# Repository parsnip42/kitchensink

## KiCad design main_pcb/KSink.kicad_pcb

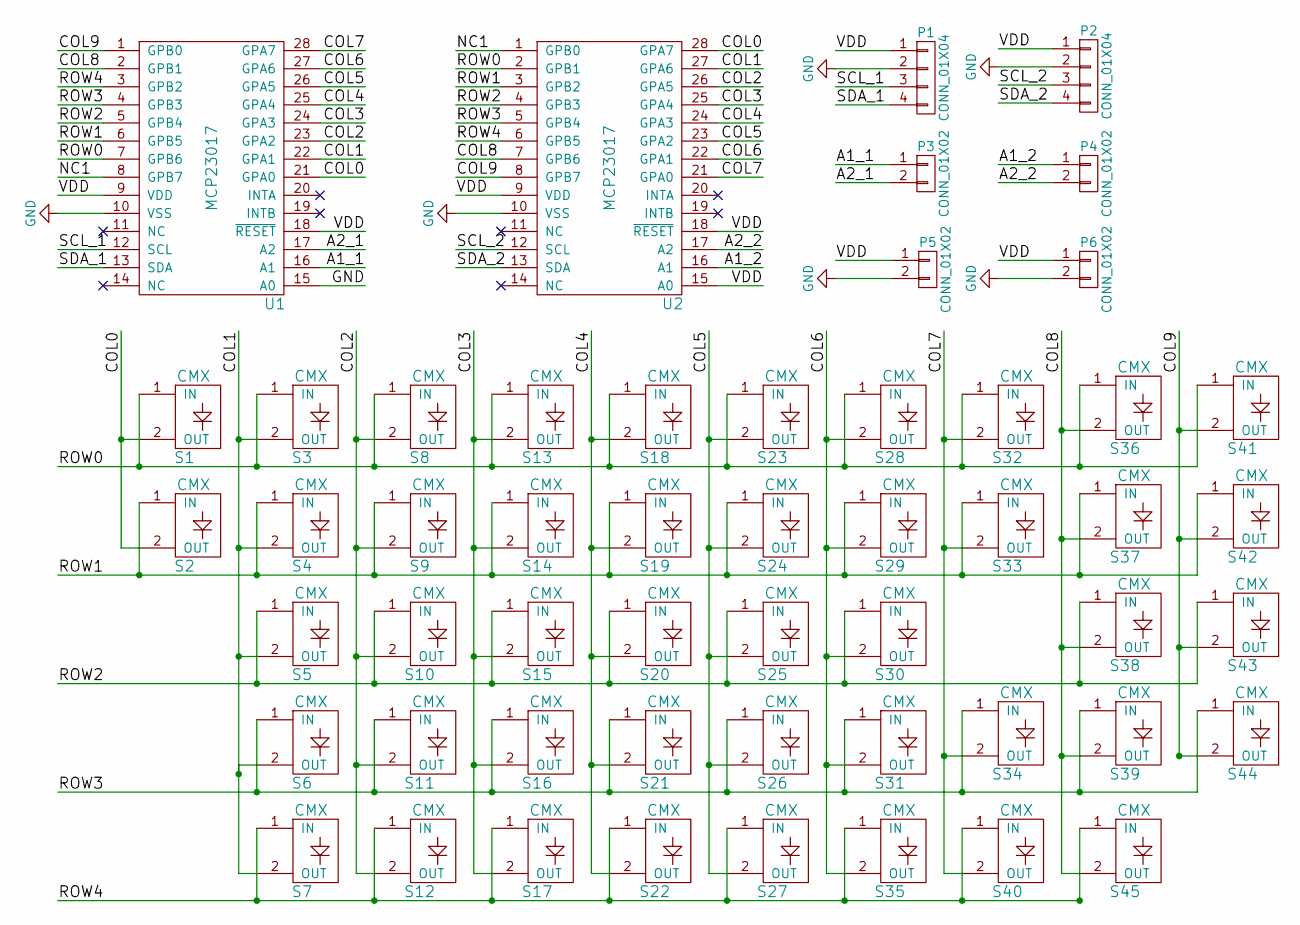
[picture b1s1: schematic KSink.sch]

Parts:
P1, P2: CONN_01X04; CONN_4X1
P3, P4, P5, P6: CONN_01X02; CONN_2X1
S1, S2, S3, S4, S5, S6, S7, S8, S9, S10, S11, S12, S13, S14, S15, S16, S17, S18, S19, S20, S21, S22, S23, S24, S25, S26, S27, S28, S29, S30, S31, S32, S33, S34, S35, S36, S37, S38, S39, S40, S41, S42, S43, S44, S45: CMX
U1, U2: MCP23017; MCP23017_DIP

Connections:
/A1_1: P3.1, U1.16 (A1)
/A1_2: P4.1, U2.16 (A1)
/A2_1: P3.2, U1.17 (A2)
/A2_2: P4.2, U2.17 (A2)
/COL0: S1.2 (OUT), S2.2 (OUT), U1.21 (GPA0), U2.28 (GPA7)
/COL1: S3.2 (OUT), S4.2 (OUT), S5.2 (OUT), S6.2 (OUT), S7.2 (OUT), U1.22 (GPA1), U2.27 (GPA6)
/COL2: S8.2 (OUT), S9.2 (OUT), S10.2 (OUT), S11.2 (OUT), S12.2 (OUT), U1.23 (GPA2), U2.26 (GPA5)
/COL3: S13.2 (OUT), S14.2 (OUT), S15.2 (OUT), S16.2 (OUT), S17.2 (OUT), U1.24 (GPA3), U2.25 (GPA4)
/COL4: S18.2 (OUT), S19.2 (OUT), S20.2 (OUT), S21.2 (OUT), S22.2 (OUT), U1.25 (GPA4), U2.24 (GPA3)
/COL5: S23.2 (OUT), S24.2 (OUT), S25.2 (OUT), S26.2 (OUT), S27.2 (OUT), U1.26 (GPA5), U2.23 (GPA2)
/COL6: S28.2 (OUT), S29.2 (OUT), S30.2 (OUT), S31.2 (OUT), S35.2 (OUT), U1.27 (GPA6), U2.22 (GPA1)
/COL7: S32.2 (OUT), S33.2 (OUT), S34.2 (OUT), S40.2 (OUT), U1.28 (GPA7), U2.21 (GPA0)
/COL8: S36.2 (OUT), S37.2 (OUT), S38.2 (OUT), S39.2 (OUT), S45.2 (OUT), U1.2 (GPB1), U2.7 (GPB6)
/COL9: S41.2 (OUT), S42.2 (OUT), S43.2 (OUT), S44.2 (OUT), U1.1 (GPB0), U2.8 (GPB7)
/NC1: U1.8 (GPB7), U2.1 (GPB0)
/ROW0: S1.1 (IN), S3.1 (IN), S8.1 (IN), S13.1 (IN), S18.1 (IN), S23.1 (IN), S28.1 (IN), S32.1 (IN), S36.1 (IN), S41.1 (IN), U1.7 (GPB6), U2.2 (GPB1)
/ROW1: S2.1 (IN), S4.1 (IN), S9.1 (IN), S14.1 (IN), S19.1 (IN), S24.1 (IN), S29.1 (IN), S33.1 (IN), S37.1 (IN), S42.1 (IN), U1.6 (GPB5), U2.3 (GPB2)
/ROW2: S5.1 (IN), S10.1 (IN), S15.1 (IN), S20.1 (IN), S25.1 (IN), S30.1 (IN), S38.1 (IN), S43.1 (IN), U1.5 (GPB4), U2.4 (GPB3)
/ROW3: S6.1 (IN), S11.1 (IN), S16.1 (IN), S21.1 (IN), S26.1 (IN), S31.1 (IN), S34.1 (IN), S39.1 (IN), S44.1 (IN), U1.4 (GPB3), U2.5 (GPB4)
/ROW4: S7.1 (IN), S12.1 (IN), S17.1 (IN), S22.1 (IN), S27.1 (IN), S35.1 (IN), S40.1 (IN), S45.1 (IN), U1.3 (GPB2), U2.6 (GPB5)
/SCL_1: P1.3, U1.12 (SCL)
/SCL_2: P2.3, U2.12 (SCL)
/SDA_1: P1.4, U1.13 (SDA)
/SDA_2: P2.4, U2.13 (SDA)
/VDD: P1.1, P2.1, P5.1, P6.1, U1.9 (VDD), U1.18 (~RESET), U2.9 (VDD), U2.15 (A0), U2.18 (~RESET)
GND: P1.2, P2.2, P5.2, P6.2, U1.10 (VSS), U1.15 (A0), U2.10 (VSS)

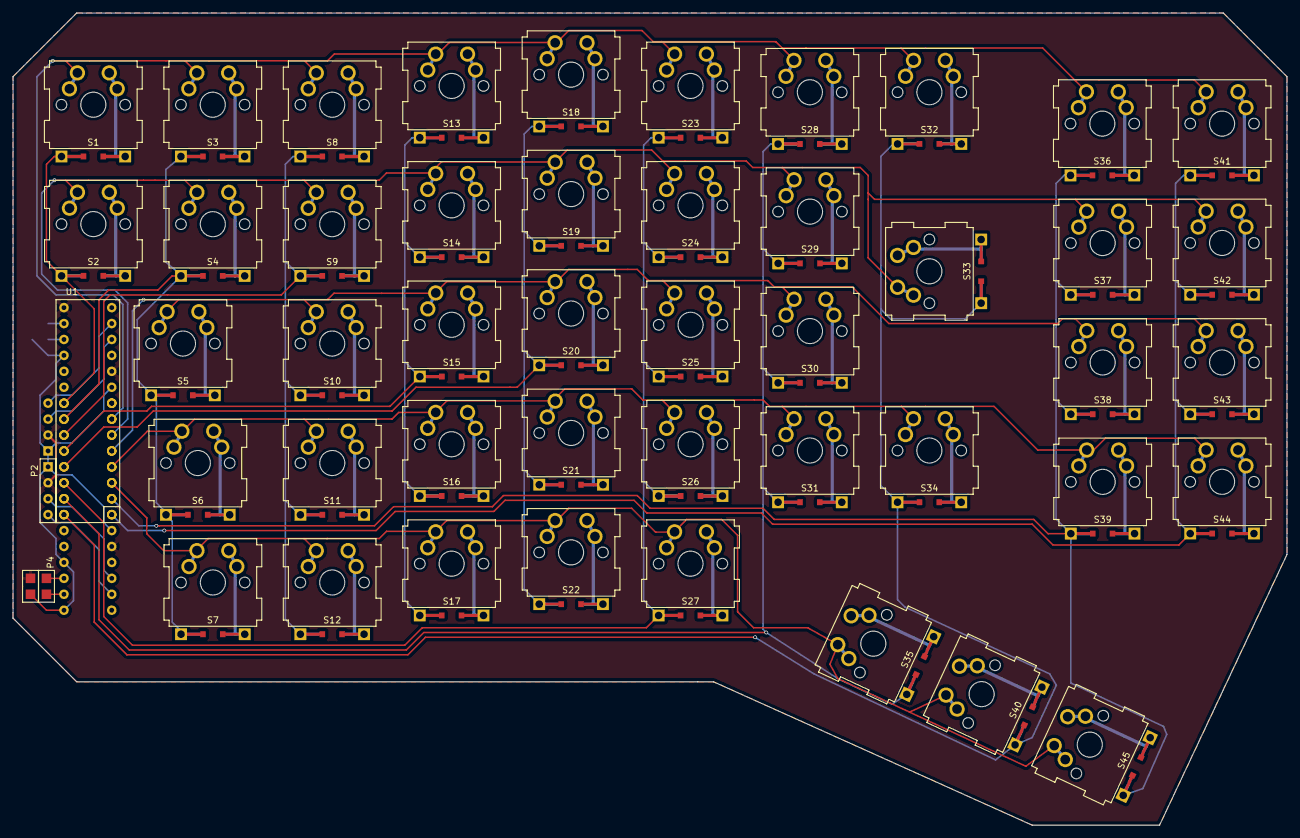
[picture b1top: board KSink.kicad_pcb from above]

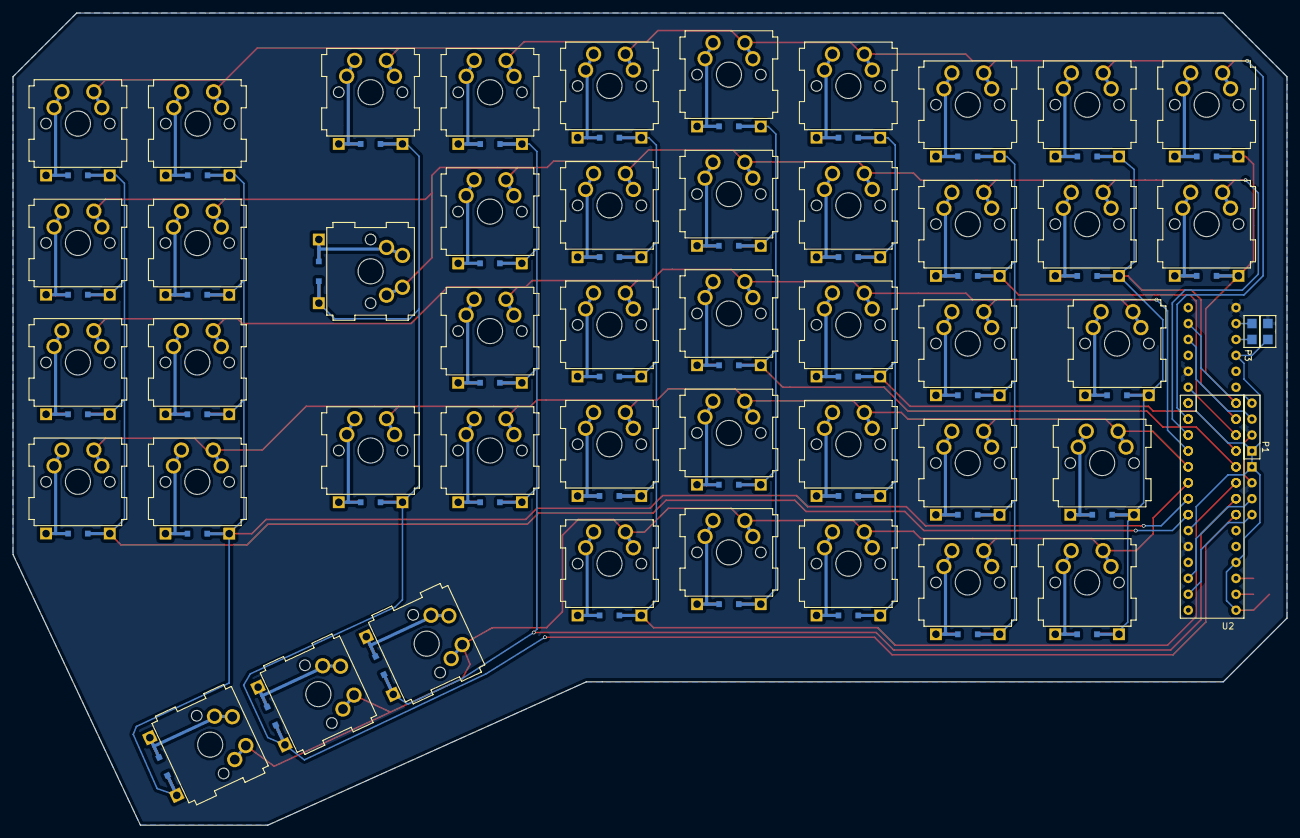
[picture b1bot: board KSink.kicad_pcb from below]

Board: 2 copper layers, 203.2 x 129.5 mm, 53 parts (4 on the bottom side), 26 nets.

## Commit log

2016-07-11 Matrix PCB
2016-07-11 DXF files for case
